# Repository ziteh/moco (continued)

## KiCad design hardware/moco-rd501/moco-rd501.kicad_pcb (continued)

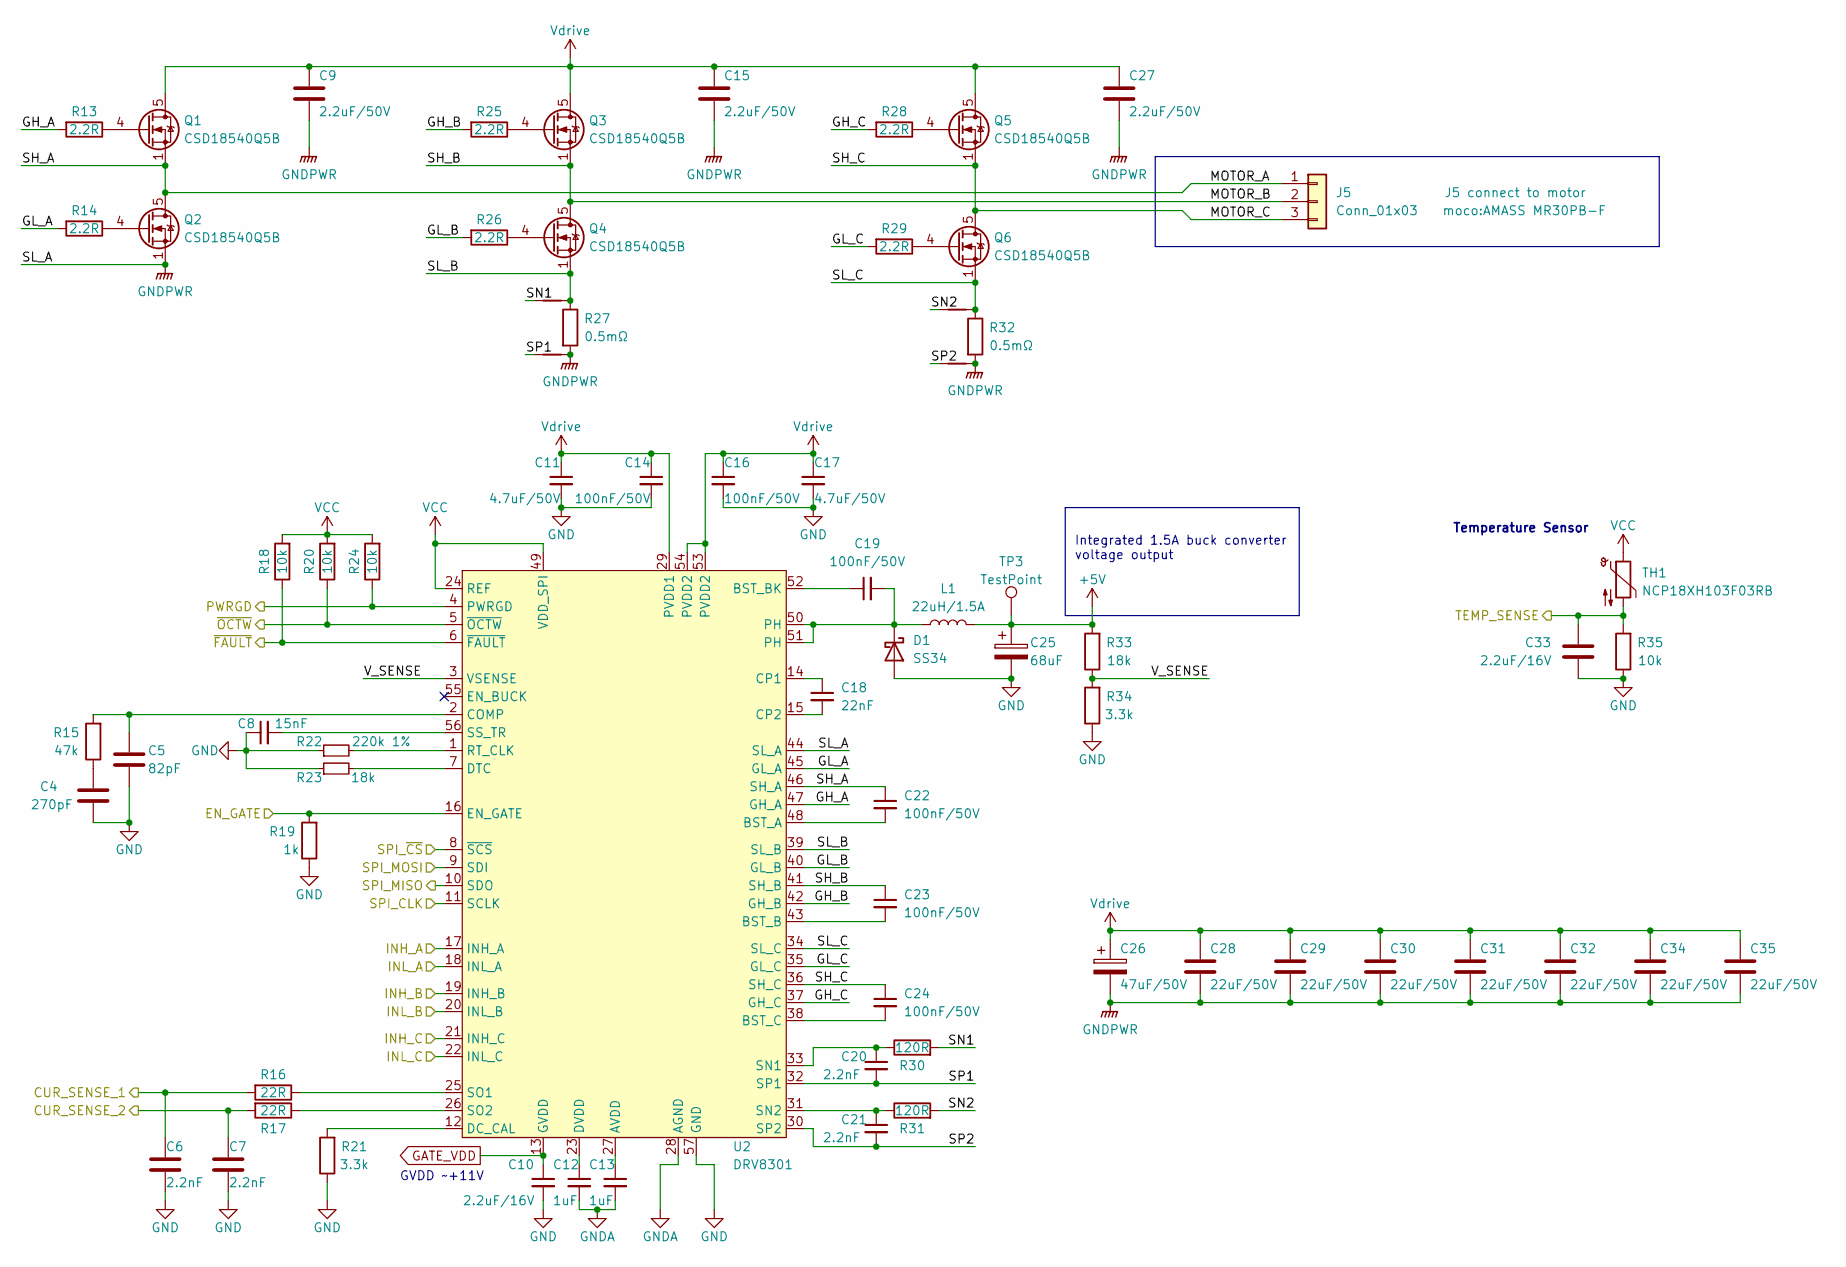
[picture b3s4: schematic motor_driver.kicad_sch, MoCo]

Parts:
C4: 270pF; C_0402_1005Metric; MFR.Part # GCM1555C1H271JA16D; JLCPCB Part # C524551
C5: 82pF; C_0402_1005Metric; MFR.Part # CC0402JRNPO9BN820; JLCPCB Part # C107011
C6, C7, C20, C21: 2.2nF; C_0603_1608Metric; MFR.Part # 0603B222K500NT; JLCPCB Part # C1604
C8: 15nF; C_0402_1005Metric; MFR.Part # CC0402KRX7R9BB153; JLCPCB Part # C114405
C9, C15, C27: 2.2uF/50V; C_1206_3216Metric; MFR.Part # CL31B225KBHNNNE; JLCPCB Part # C50254
C10, C33: 2.2uF/16V; C_0402_1005Metric; MFR.Part # 0402X225K160NT; JLCPCB Part # C501836
C11, C17: 4.7uF/50V; C_1206_3216Metric; MFR.Part # 1206B475K500NT; JLCPCB Part # C29823
C12, C13: 1uF; C_0402_1005Metric; MFR.Part # CL05A105KA5NQNC; JLCPCB Part # C52923
C14, C16, C19, C22, C23, C24: 100nF/50V; C_0603_1608Metric; MFR.Part # CC0603KRX7R9BB104; JLCPCB Part # C14663
C18: 22nF; C_0402_1005Metric; MFR.Part # 0402B223K500NT; JLCPCB Part # C1532
C25: 68uF; CP_EIA-6032-28_Kemet-C; MFR.Part # TAJC686K016RNJ; JLCPCB Part # C7220
C26: 47uF/50V; CP_Elec_6.3x7.7; MFR.Part # VES470M1HTR-0607; JLCPCB Part # C108053
C28, C29, C30, C31, C32, C34, C35: 22uF/50V; C_1210_3225Metric_Pad1.33x2.70mm_HandSolder
D1: SS34; D_SMA; MFR.Part # SS34; JLCPCB Part # C8678
J5: Conn_01x03; AMASS MR30PB-F; MFR.Part # MR30PB-F
L1: 22uH/1.5A; L_Bourns-SRN8040_8x8.15mm; MFR.Part # CKCS8040-22uH/M; JLCPCB Part # C354640
NT1, NT2, NT3, NT4: NetTie_2; NetTie-2_SMD_Pad0.5mm
Q1, Q2, Q3, Q4, Q5, Q6: CSD18540Q5B; TDSON-8-1; MFR.Part # CSD18540Q5B; JLCPCB Part # C86513
R13, R14, R25, R26, R28, R29: 2.2R; R_0603_1608Metric; MFR.Part # 0603WAF220KT5E; JLCPCB Part # C22939
R15: 47k; R_0402_1005Metric; MFR.Part # 0402WGF4702TCE; JLCPCB Part # C25792
R16, R17: 22R; R_0402_1005Metric; MFR.Part # 0402WGF220JTCE; JLCPCB Part # C25092
R18, R20, R24, R35: 10k; R_0402_1005Metric; MFR.Part # 0402WGF1002TCE; JLCPCB Part # C25744
R19: 1k; R_0402_1005Metric; MFR.Part # 0402WGF1001TCE; JLCPCB Part # C11702
R21, R34: 3.3k; R_0402_1005Metric; MFR.Part # 0402WGF3301TCE; JLCPCB Part # C25890
R22: 220k 1%; R_0402_1005Metric; MFR.Part # 0402WGF2203TCE; JLCPCB Part # C25767
R23, R33: 18k; R_0402_1005Metric; MFR.Part # 0402WGF1802TCE; JLCPCB Part # C25762
R27, R32: 0.5mΩ; R_2512_6332Metric; MFR.Part # ASR-M-3-0.5F; JLCPCB Part # C469426
R30, R31: 120R; R_0402_1005Metric; MFR.Part # 0402WGF1200TCE; JLCPCB Part # C25079
TH1: NCP18XH103F03RB; R_0603_1608Metric; MFR.Part # NCP18XH103F03RB; JLCPCB Part # C13564
TP3: TestPoint; TestPoint_Pad_D2.0mm
U2: DRV8301; HTSSOP-56-1EP_6.1x14mm_P0.5mm_EP3.61x6.35mm; MFR.Part # DRV8301DCAR; JLCPCB Part # C98969

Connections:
+5V: C25.1, L1.2, R33.2, TP3.1; also elsewhere on the board
/EN_GATE: R19.2, U2.16 (EN_GATE); also elsewhere on the board
/MCU/CURR_SENSE_1: C6.1, R16.2; also elsewhere on the board
/MCU/CURR_SENSE_2: C7.1, R17.2; also elsewhere on the board
/MCU/PWM_AH: U2.17 (INH_A); also elsewhere on the board
/MCU/PWM_AL: U2.18 (INL_A); also elsewhere on the board
/MCU/PWM_BH: U2.19 (INH_B); also elsewhere on the board
/MCU/PWM_BL: U2.20 (INL_B); also elsewhere on the board
/MCU/PWM_CH: U2.21 (INH_C); also elsewhere on the board
/MCU/PWM_CL: U2.22 (INL_C); also elsewhere on the board
/MCU/TEMP_SENSE: C33.1, R35.2, TH1.2; also elsewhere on the board
/Motor Driver/GH_A: R13.2, U2.47 (GH_A)
/Motor Driver/GH_B: R25.2, U2.42 (GH_B)
/Motor Driver/GH_C: R28.2, U2.37 (GH_C)
/Motor Driver/GL_A: R14.2, U2.45 (GL_A)
/Motor Driver/GL_B: R26.2, U2.40 (GL_B)
/Motor Driver/GL_C: R29.2, U2.35 (GL_C)
/Motor Driver/MOTOR_A: C22.1, J5.1, Q1.1 (S), Q1.2 (S), Q1.3 (S), Q2.5 (D), U2.46 (SH_A)
/Motor Driver/MOTOR_B: C23.1, J5.2, Q3.1 (S), Q3.2 (S), Q3.3 (S), Q4.5 (D), U2.41 (SH_B)
/Motor Driver/MOTOR_C: C24.1, J5.3, Q5.1 (S), Q5.2 (S), Q5.3 (S), Q6.5 (D), U2.36 (SH_C)
/Motor Driver/PWRGD: R24.1, U2.4 (PWRGD)
/Motor Driver/SL_B: NT1.2, Q4.1 (S), Q4.2 (S), Q4.3 (S), R27.1, U2.39 (SL_B)
/Motor Driver/SL_C: NT3.2, Q6.1 (S), Q6.2 (S), Q6.3 (S), R32.1, U2.34 (SL_C)
/Motor Driver/SN1: NT1.1, R30.2
/Motor Driver/SN2: NT3.1, R31.2
/Motor Driver/SP1: C20.2, NT2.1, U2.32 (SP1)
/Motor Driver/SP2: C21.2, NT4.1, U2.30 (SP2)
/Motor Driver/V_SENSE: R33.1, R34.2, U2.3 (VSENSE)
/Motor Driver/~OCTW: R20.1, U2.5 (~OCTW)
/SPI_CLK: U2.11 (SCLK); also elsewhere on the board
/SPI_DRIVER_~CS: U2.8 (~SCS); also elsewhere on the board
/SPI_MISO: U2.10 (SDO); also elsewhere on the board
/SPI_MOSI: U2.9 (SDI); also elsewhere on the board
/~FAULT: R18.1, U2.6 (~FAULT); also elsewhere on the board
GATE_VDD: C10.1, U2.13 (GVDD)
GND: C4.2, C5.2, C6.2, C7.2, C8.1, C9.2, C10.2, C11.2, C12.2, C13.2, C14.2, C15.2, C16.2, C17.2, C25.2, C26.2, C27.2, C28.2, C29.2, C30.2, C31.2, C32.2, C33.2, C34.2, C35.2, D1.2 (A), NT2.2, NT4.2, Q2.1 (S), Q2.2 (S), Q2.3 (S), R19.1, R21.1, R22.1, R23.1, R27.2, R32.2, R34.1, R35.1, U2.28 (AGND), U2.44 (SL_A), U2.57 (GND); also elsewhere on the board
unnamed: C4.1, R15.1
unnamed: C5.1, R15.2, U2.2 (COMP)
unnamed: C8.2, U2.56 (SS_TR)
unnamed: C12.1, U2.23 (DVDD)
unnamed: C13.1, U2.27 (AVDD)
unnamed: C18.1, U2.14 (CP1)
unnamed: C18.2, U2.15 (CP2)
unnamed: C19.1, U2.52 (BST_BK)
unnamed: C19.2, D1.1 (K), L1.1, U2.50 (PH), U2.51 (PH)
unnamed: C20.1, R30.1, U2.33 (SN1)
unnamed: C21.1, R31.1, U2.31 (SN2)
unnamed: C22.2, U2.48 (BST_A)
unnamed: C23.2, U2.43 (BST_B)
unnamed: C24.2, U2.38 (BST_C)
unnamed: Q1.4 (G), R13.1
unnamed: Q2.4 (G), R14.1
unnamed: Q3.4 (G), R25.1
unnamed: Q4.4 (G), R26.1
unnamed: Q5.4 (G), R28.1
unnamed: Q6.4 (G), R29.1
unnamed: R16.1, U2.25 (SO1)
unnamed: R17.1, U2.26 (SO2)
unnamed: R21.2, U2.12 (DC_CAL)
unnamed: R22.2, U2.1 (RT_CLK)
unnamed: R23.2, U2.7 (DTC)
VCC: R18.2, R20.2, R24.2, TH1.1, U2.24 (REF), U2.49 (VDD_SPI); also elsewhere on the board
Vdrive: C9.1, C11.1, C14.1, C15.1, C16.1, C17.1, C26.1, C27.1, C28.1, C29.1, C30.1, C31.1, C32.1, C34.1, C35.1, Q1.5 (D), Q3.5 (D), Q5.5 (D), U2.29 (PVDD1), U2.53 (PVDD2), U2.54 (PVDD2); also elsewhere on the board

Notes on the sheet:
Integrated 1.5A buck converter voltage output
Temperature Sensor
GVDD ~+11V

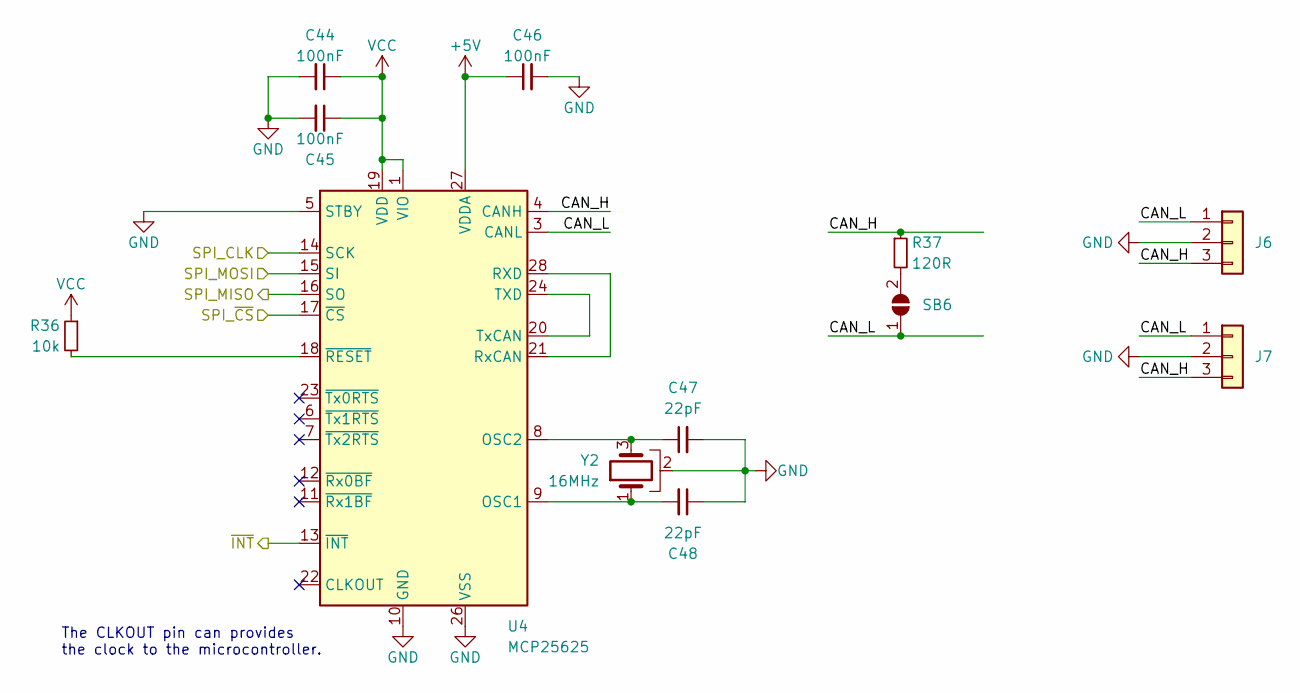
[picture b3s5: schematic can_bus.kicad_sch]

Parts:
C44, C45, C46: 100nF; C_0402_1005Metric; MFR.Part # CL05B104KO5NNNC; JLCPCB Part # C1525
C47, C48: 22pF; C_0402_1005Metric; MFR.Part # 0402CG220J500NT; JLCPCB Part # C1555
J6, J7: Conn_02x02_Top_Bottom; JST_GH_SM03B-GHS-TB_1x03-1MP_P1.25mm_Horizontal; MFR.Part # GH1.25-3PWBPZ; JLCPCB Part # C2829252
R36: 10k; R_0402_1005Metric; MFR.Part # 0402WGF1002TCE; JLCPCB Part # C25744
R37: 120R; R_0402_1005Metric; MFR.Part # 0402WGF1200TCE; JLCPCB Part # C25079
SB6: SolderJumper_2_Open; SolderJumper-2_P1.3mm_Open_TrianglePad1.0x1.5mm
U4: MCP25625; QFN-28-1EP_6x6mm_P0.65mm_EP4.25x4.25mm; MFR.Part # MCP25625T-E/ML; JLCPCB Part # C191253
Y2: 16MHz; Crystal_SMD_3225-4Pin_3.2x2.5mm; MFR.Part # X322516MLB4SI; JLCPCB Part # C13738

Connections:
+5V: C46.1, U4.27 (VDDA); also elsewhere on the board
/CAN BUS/CAN_H: J6.3, J7.3, R37.1, U4.4 (CANH)
/CAN BUS/CAN_L: J6.1, J7.1, SB6.1 (A), U4.3 (CANL)
/CAN BUS/~INT: U4.13 (~INT); also elsewhere on the board
/SPI_CAN_~CS: U4.17 (~CS); also elsewhere on the board
/SPI_CLK: U4.14 (SCK); also elsewhere on the board
/SPI_MISO: U4.16 (SO); also elsewhere on the board
/SPI_MOSI: U4.15 (SI); also elsewhere on the board
GND: C44.2, C45.2, C46.2, C47.2, C48.1, J6.2, J7.2, U4.5 (STBY), U4.10 (GND), U4.26 (VSS), Y2.2; also elsewhere on the board
unnamed: C47.1, U4.8 (OSC2), Y2.3
unnamed: C48.2, U4.9 (OSC1), Y2.1
unnamed: R36.2, U4.18 (~RESET)
unnamed: R37.2, SB6.2 (B)
unnamed: U4.20 (TxCAN), U4.24 (TXD)
unnamed: U4.21 (RxCAN), U4.28 (RXD)
VCC: C44.1, C45.1, R36.1, U4.1 (VIO), U4.19 (VDD); also elsewhere on the board

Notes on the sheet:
The CLKOUT pin can provides the clock to the microcontroller.

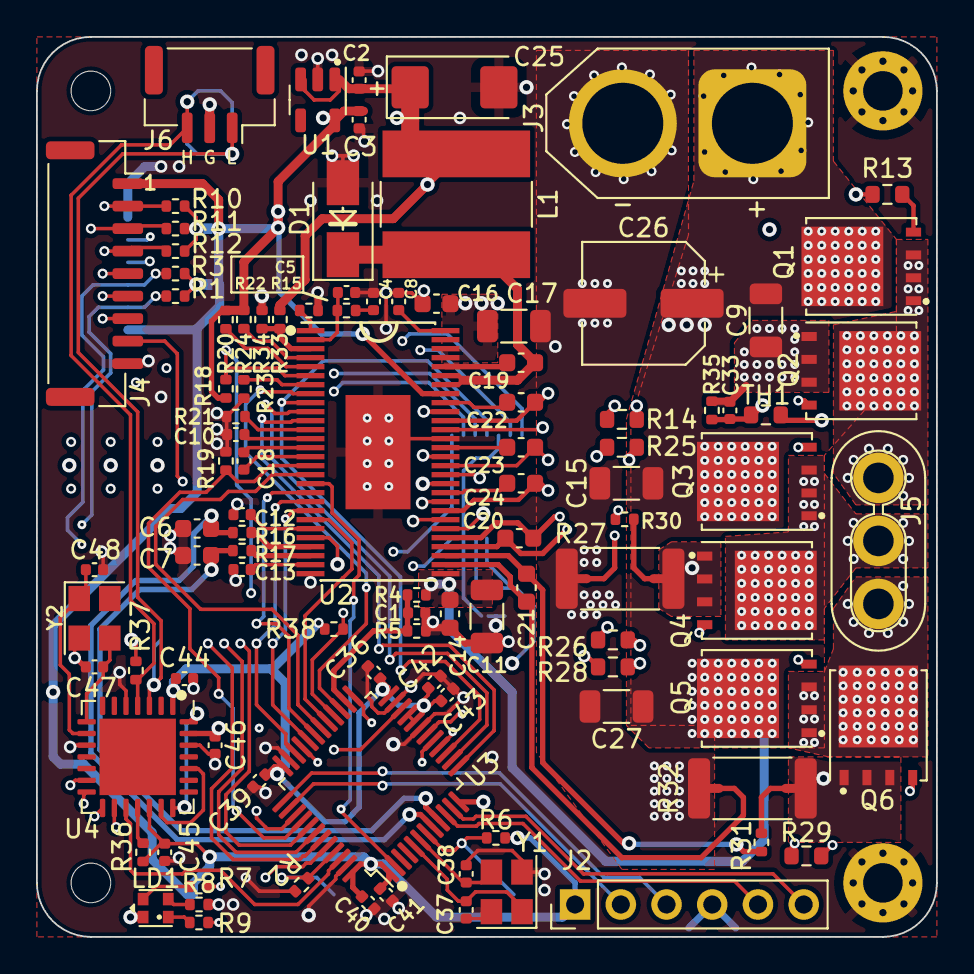
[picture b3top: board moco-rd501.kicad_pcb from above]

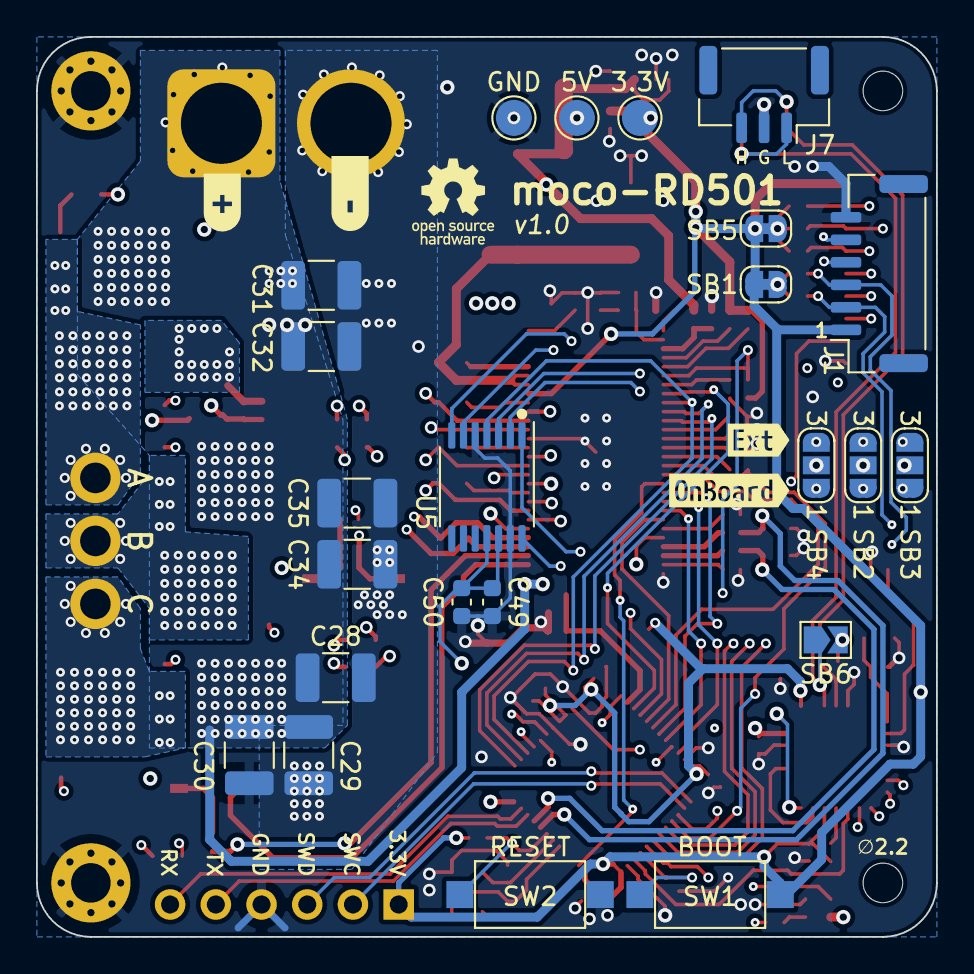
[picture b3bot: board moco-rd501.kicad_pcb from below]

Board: 4 copper layers, 50.0 x 50.0 mm, 135 parts (27 on the bottom side), 103 nets.

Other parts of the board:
kibuzzard-638C8B7C: G***; kibuzzard-638C8B7C
kibuzzard-638C8BCF: G***; kibuzzard-638C8BCF
kibuzzard-638C8E4D: G***; kibuzzard-638C8E4D
kibuzzard-638C8E29: G***; kibuzzard-638C8E29

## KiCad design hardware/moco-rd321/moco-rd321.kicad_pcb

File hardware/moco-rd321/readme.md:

# moco-RD321

- 6.7V~35V, 12A
- 3-Phase low-side current sensing. OP-Amp Gain=6.74, Shunt resistor=20mΩ
- Overcurrent detection. Ith=30A @ OC_COMPth=500mV
- Input voltage sensing
- 32x32mm square PCB, 4xM2 mounting holes
- [STSPIN32F0A](https://www.st.com/en/motor-drivers/stspin32f0a.html) 3-phase gate driver with embdded MCU SiP
  - STM32F031C6 48MHz, 4KB SRAM, 32KB Flash
  - 600mA sink/source gate drivers, integrated bootstrap diodes
  - 12V LDO and 3.3V buck
- [SiZ250DT](https://www.vishay.com/en/product/77227/) Dual N-MOSFET, 60V, 38A, 3.3x3.3mm
- MA702 magnetic encoder, SPI
- 2x04 2.54mm Pin header for debug, JST SM03B-SRSS-TB 1x03 for Serial and I2C

## Pinmap

| Description              | Analog IC    | STM32 | STM32 Func       |
| ------------------------ | ------------ | ----- | ---------------- |
| High-side U              | HS1          | PA8   | TIM1_CH1         |
| High-side V              | HS2          | PA9   | TIM1_CH2         |
| High-side W              | HS3          | PA10  | TIM1_CH3         |
| Low-side U               | LS1          | PB13  | TIM1_CH1N        |
| Low-side V               | LS2          | PB14  | TIM1_CH2N        |
| Low-side W               | LS3          | PB15  | TIM1_CH3N        |
| OC threshold select 1    | OC_TH_STBY1  | PF7   | Push-pull output |
| OC threshold select 2    | OC_TH_STBY2  | PF6   | Push-pull output |
| OC protection selection  | OC_SEL       | PA11  | Push-pull output |
| OC comparator output     | OC_COMP_INT  | PB12  | TIM1_BKIN        |
| OC comparator output     | OC_COMP_INT2 | PA12  | TIM1_ETR         |
| Current sense U          | OP3O         | PA0   | ADC_IN0          |
| Current sense V          | OP2O         | PA1   | ADC_IN1          |
| Current sense W          | OP1O         | PB1   | ADC_IN9          |
| VM sense                 | --           | PA4   | ADC_IN4          |
| SPI SCLK                 | --           | PA5   | SPI1             |
| SPI MISO                 | --           | PA6   | SPI1             |
| SPI MOSI                 | --           | PA7   | SPI1             |
| SPI nCS MA702            | --           | PA15  |                  |
| USART Tx                 | --           | PA2   | USART1           |
| USART Rx                 | --           | PA3   | USART1           |
| I2C SCL                  | --           | PB6   | I2C1             |
| I2C SDA                  | --           | PB7   | I2C1             |
| SWDIO                    | --           | PA13  |                  |
| SWCLK                    | --           | PA14  |                  |
| Connected to GND         | --           | BOOT0 |                  |
| User LED (Red)           | --           | PF0   | Active HIGH      |
| 12V indicator LED (Blue) | --           | --    |                  |

> - Unused GPIOs inside the package should be config to output low: PB0, PB2, PB3, PB4, PB5, PB8, PB9, PB10, PB11, PC13, PC14, PC15.
> - OC_TH_STBY1 and OC_TH_STBY2 should be HIGH for 500mV OC threshold.
> - For analog IC, the GPIO input config without pull-up or -down is always allowed.

## PCB

### Jumper

If input voltage (i.e. VM)<15V then close `SB1` to connect VM pin and VREG12 pin.

### Board Characteristics

- Copper layer count: 4
- Board overall dimensions: 32 x 32 mm
- Min track/spacing: 0.13 mm / 0.13 mm
- Min hole diameter: 0.3 mm
- Castellated pads: No
- Edge card connectors: No
- Plated board edge: No
- 1oz copper

## SPI

MA702 encoder SPI:
- Mode:
  - 0 (CPOL=0, CPHA=0) or 1 (CPOL=1, CPHA=1)
  - Data sampled on first edge
- 16-bit data frame
- MSB first
- nCS pin active low
- 25MHz clock

## MCU

| STSPIN32*x*                         | [F0](https://www.st.com/en/motor-drivers/stspin32f0.html) | [F0***A***](https://www.st.com/en/motor-drivers/stspin32f0a.html) | [F0***B***](https://www.st.com/en/motor-drivers/stspin32f0b.html) |
| ----------------------------------- | --------------------------------------------------------- | ----------------------------------------------------------------- | ----------------------------------------------------------------- |
| Operating voltage                   | 8~45V                                                     | 6.7~45V                                                           | 6.7~45V                                                           |
| OP-Amps                             | 4                                                         | 3                                                                 | 1                                                                 |
| GPIOs                               | 15                                                        | 16                                                                | 20                                                                |
| BOOT0 pin                           | --                                                        | Yes                                                               | Yes                                                               |
| 3FG decoding logic for Hall sensors | Yes                                                       | --                                                                | --                                                                |
| Comparator                          | OCP                                                       | OCP and current control                                           | OCP and current control                                           |
| Package                             | QFN 7x7mm 1EP                                             | QFN 7x7mm 1EP                                                     | QFN 7x7mm 1EP                                                     |

> [Solved: STSPIN32F0 vs STSPIN32F0A vs STSPIN32F0B - STMicroelectronics Community](https://community.st.com/t5/power-management/stspin32f0-vs-stspin32f0a-vs-stspin32f0b/td-p/273388)

## Reference

- [qwertpas/O32controller: Miniature closed-loop controller for brushless DC motors](https://github.com/qwertpas/O32controller)
- [STspin32G4 support - hardware support - SimpleFOC Community](https://community.simplefoc.com/t/stspin32g4-support/2027/6?page=3)
- ST AN5397 *"Current Sensing in motion control applications"*
- ST AN4999 *"STSPIN32F0/F0A/F0B overcurrent protection"*
- ST DB3364 *"STEVAL-SPIN3202: STSPIN32F0A advanced 3-phase BLDC driver with embedded STM32 MCU single shunt evaluation board"*
- ST DB4049 *"EVALKIT-ROBOT-1: Compact reference design kit for robotics and automation based on STSPIN32F0A"*
- ST DB3798 *"STEVAL-ESC002V1: Electronic Speed Controller reference design based on STSPIN32F0A"*
- TI SLUA887 *"Bootstrap Circuitry Selection for Half-Bridge Configurations"*
- Diodes DN1156 *"Gate Drivers in BLDC Motors"*

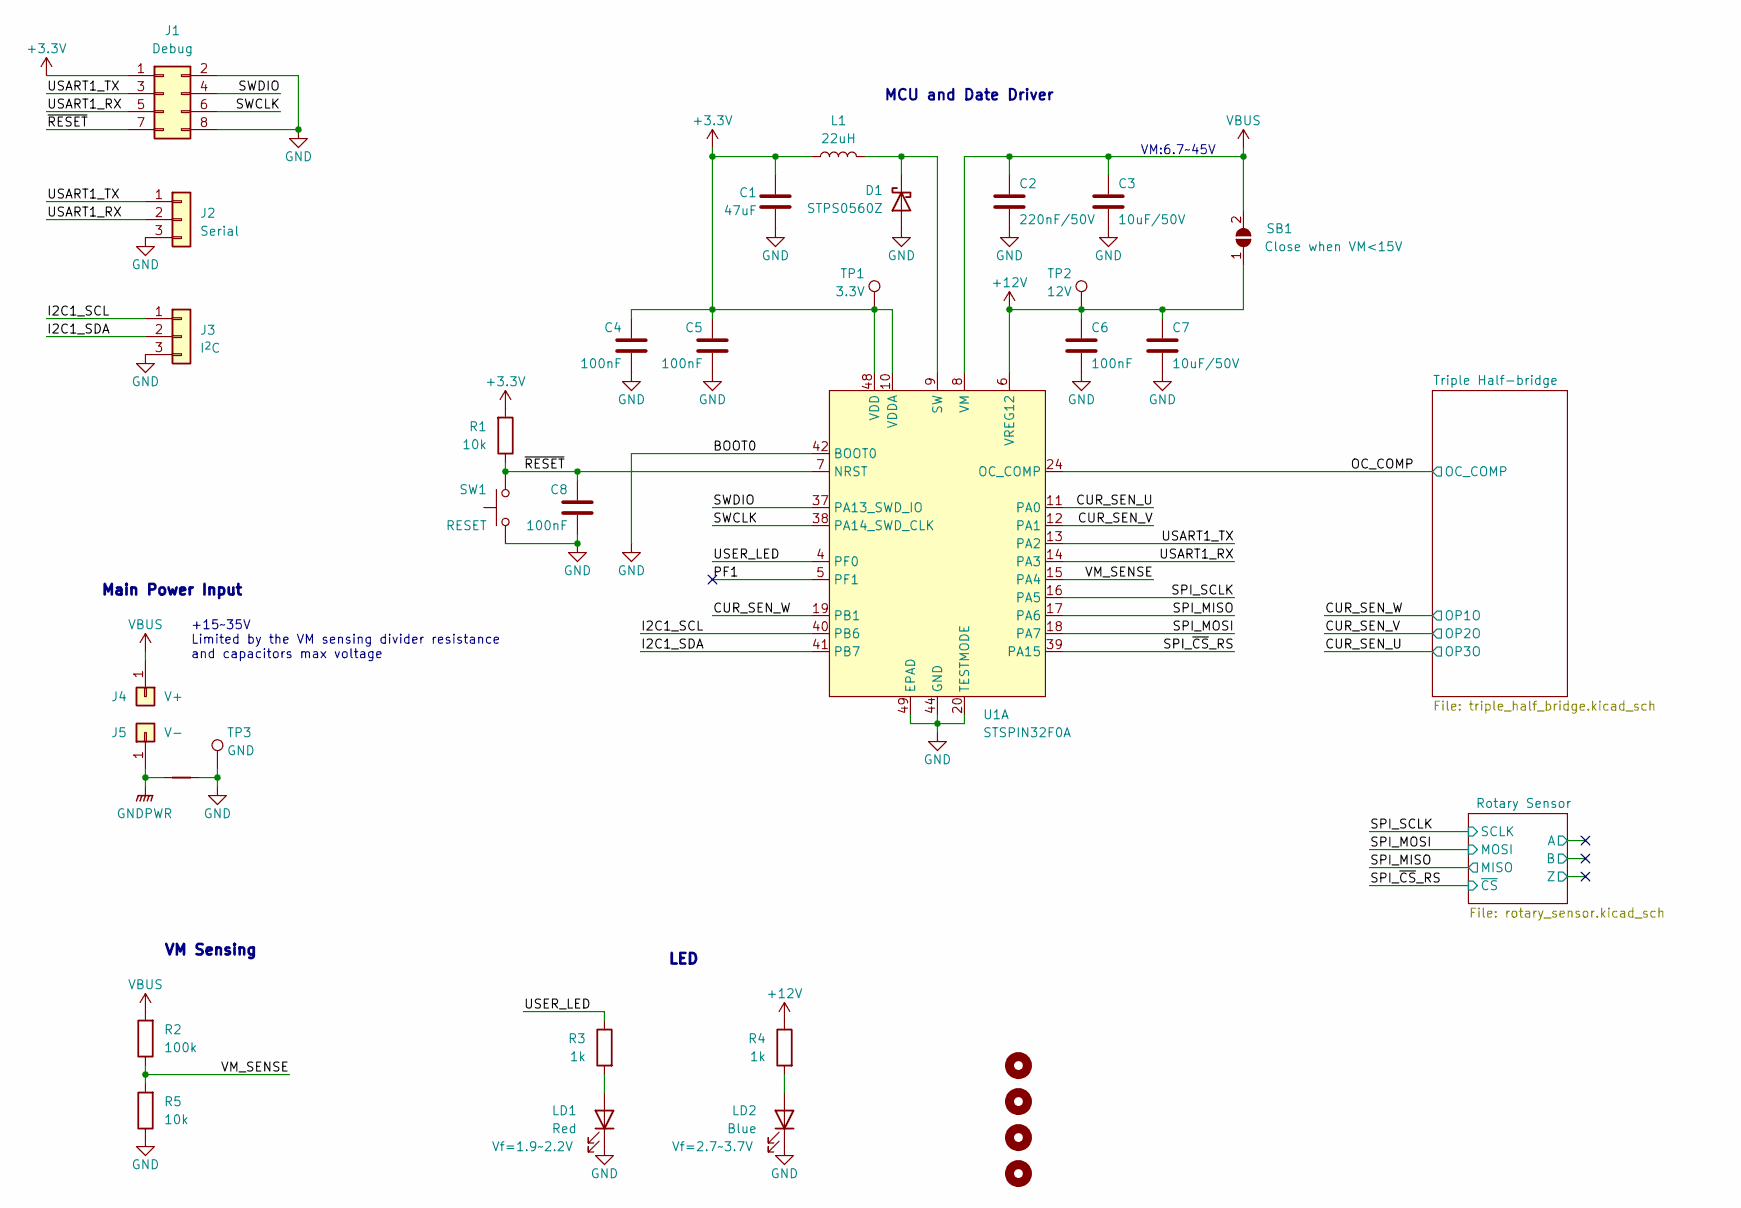
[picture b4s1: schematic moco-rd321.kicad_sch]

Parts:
C1: 47uF; C_0805_2012Metric; MFR. Part# CL21A476MQYNNNE; LCSC C16780
C2: 220nF/50V; C_0805_2012Metric; MFR. Part# CL21B224KBFNNNE; LCSC C5378
C3, C7: 10uF/50V; C_0805_2012Metric; MFR. Part# GRM21BR61H106KE43L; LCSC C440198
C4, C5, C6, C8: 100nF; C_0402_1005Metric; MFR. Part# CL05B104KB54PNC; LCSC C307331
D1: STPS0560Z; D_SOD-123F; MFR. Part# STPS0560Z; LCSC C99285
H1, H2, H3, H4: MountingHole; MountingHole_2.2mm_M2_ISO14580
J1: Debug; PinHeader_2x04_P2.54mm_Vertical
J2: Serial; JST_SH_SM03B-SRSS-TB_1x03-1MP_P1.00mm_Horizontal; MFR. Part# SM03B-SRSS-TB(LF)(SN); LCSC C160403
J3: I^{2}C; JST_SH_SM03B-SRSS-TB_1x03-1MP_P1.00mm_Horizontal; MFR. Part# SM03B-SRSS-TB(LF)(SN); LCSC C160403
J4: V+; wire_2.2mm_rectagnel
J5: V-; wire_2.2mm
L1: 22uH; L_Taiyo-Yuden_MD-3030; MFR. Part# YNR3015-220M; LCSC C497564
LD1: Red; LED_0603_1608Metric; MFR. Part# KT-0603R; LCSC C2286
LD2: Blue; LED_0603_1608Metric; MFR. Part# 19-217/GHC-YR1S2/3T; LCSC C72043
NT1: NetTie_2; NetTie-2_SMD_Pad0.5mm
R1, R5: 10k; R_0402_1005Metric; MFR. Part# 0402WGF1002TCE; LCSC C25744
R2: 100k; R_0402_1005Metric; MFR. Part# 0402WGF1003TCE; LCSC C25741
R3, R4: 1k; R_0402_1005Metric; MFR. Part# 0402WGF1001TCE; LCSC C11702
SB1: SolderJumper_2_Open; SolderJumper-2_P1.3mm_Open_RoundedPad1.0x1.5mm
SW1: RESET; SW_SPST_EVQP7C; MFR. Part# 3*4mm
TP1: 3.3V; TestPoint_Pad_D1.0mm
TP2: 12V; TestPoint_Pad_D1.0mm
TP3: GND; TestPoint_Pad_D1.0mm
U1: STSPIN32F0A; VFQFN-48_7x7_EP2.8mm_Pitch0.5mm; MFR. Part# STSPIN32F0A; LCSC C1520987

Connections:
+3.3V: C1.1, C4.1, C5.1, J1.1, L1.1, R1.2, TP1.1, U1.10 (VDDA), U1.48 (VDD); also elsewhere on the board
+12V: C6.1, C7.1, R4.1, SB1.1 (A), TP2.1, U1.6 (VREG12)
/CUR_SEN_U: U1.11 (PA0); also elsewhere on the board
/CUR_SEN_V: U1.12 (PA1); also elsewhere on the board
/CUR_SEN_W: U1.19 (PB1); also elsewhere on the board
/I2C1_SCL: J3.1, U1.40 (PB6)
/I2C1_SDA: J3.2, U1.41 (PB7)
/OC_COMP: U1.24 (OC_COMP); also elsewhere on the board
/PF1: U1.5 (PF1)
/SPI_MISO: U1.17 (PA6); also elsewhere on the board
/SPI_MOSI: U1.18 (PA7); also elsewhere on the board
/SPI_SCLK: U1.16 (PA5); also elsewhere on the board
/SPI_~CS_RS: U1.39 (PA15); also elsewhere on the board
/SWCLK: J1.6, U1.38 (PA14_SWD_CLK)
/SWDIO: J1.4, U1.37 (PA13_SWD_IO)
/USART1_RX: J1.5, J2.2, U1.14 (PA3)
/USART1_TX: J1.3, J2.1, U1.13 (PA2)
/USER_LED: R3.1, U1.4 (PF0)
/VM_SENSE: R2.1, R5.2, U1.15 (PA4)
/~RESET: C8.1, J1.7, R1.1, SW1.1, U1.7 (NRST)
GND: C1.2, C2.2, C3.2, C4.2, C5.2, C6.2, C7.2, C8.2, D1.2 (A), J1.2, J1.8, J2.3, J3.3, LD1.1 (K), LD2.1 (K), NT1.2, R5.1, SW1.2, TP3.1, U1.20 (TESTMODE), U1.42 (BOOT0), U1.44 (GND), U1.49 (EPAD); also elsewhere on the board
GNDPWR: J5.1, NT1.1; also elsewhere on the board
unnamed: D1.1 (K), L1.2, U1.9 (SW)
unnamed: LD1.2 (A), R3.2
unnamed: LD2.2 (A), R4.2
VBUS: C2.1, C3.1, J4.1, R2.2, SB1.2 (B), U1.8 (VM); also elsewhere on the board

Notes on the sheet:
+15~35V Limited by the VM sensing divider resistance and capacitors max voltage
VM Sensing
VM:6.7~45V
LED
Main Power Input
MCU and Date Driver

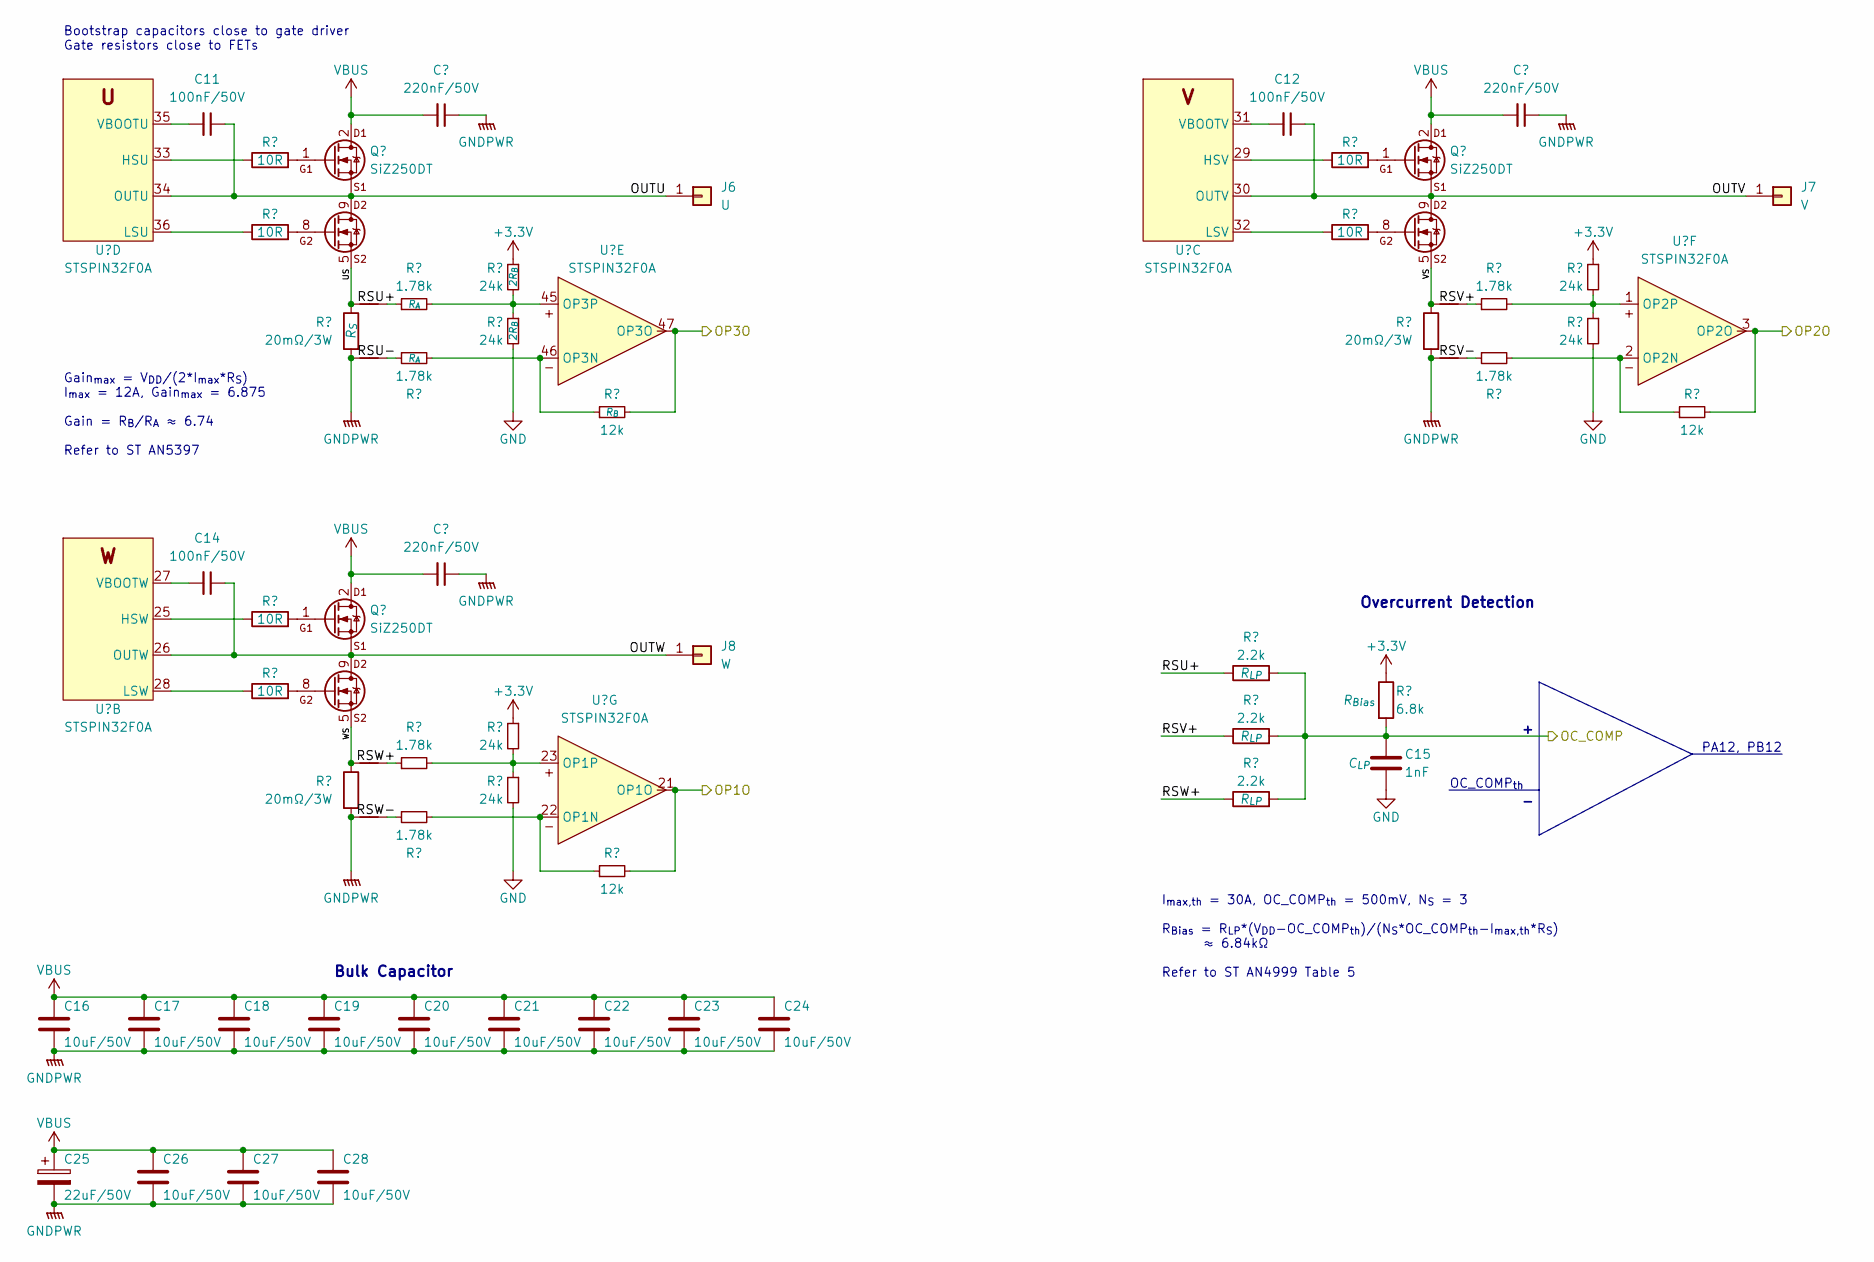
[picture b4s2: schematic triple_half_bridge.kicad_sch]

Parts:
C9, C10, C13: 220nF/50V; C_0805_2012Metric; MFR. Part# CL21B224KBFNNNE; LCSC C5378
C11, C12, C14: 100nF/50V; C_0402_1005Metric; MFR. Part# CL05B104KB54PNC; LCSC C307331
C15: 1nF; C_0402_1005Metric; MFR. Part# 0402B102K500NT; LCSC C1523
C16, C17, C18, C19, C20, C21, C22, C23, C24, C26, C27, C28: 10uF/50V; C_0805_2012Metric; MFR. Part# GRM21BR61H106KE43L; LCSC C440198
C25: 22uF/50V; CP_Elec_5x5.8; MFR. Part# EEEFT1H220AR; LCSC C336246
J6: U; wire_2.2mm
J7: V; wire_2.2mm
J8: W; wire_2.2mm
NT2, NT3, NT4, NT5, NT6, NT7: NetTie_2; NetTie-2_SMD_Pad0.5mm
Q1, Q2, Q3: SiZ250DT; PowerPAIR_3x3S_TP; MFR. Part# SIZ250DT-T1-GE3; LCSC C3279427
R6, R7, R8, R9, R22, R25: 10R; R_0402_1005Metric; MFR. Part# 0402WGF100JTCE; LCSC C25077
R10, R11, R15, R17, R27, R31: 24k; R_0402_1005Metric; MFR. Part# 0402WGF2402TCE; LCSC C25769
R12, R13, R18, R19, R28, R32: 1.78k; R_0402_1005Metric; MFR. Part# ARG02FTC1781; LCSC C284379
R14, R16, R30: 20mΩ/3W; R_2512_6332Metric; MFR. Part# CRA2512-FZ-R020ELF; LCSC C840620
R20, R21, R33: 12k; R_0402_1005Metric; MFR. Part# 0402WGF1202TCE; LCSC C25752
R23, R26, R29: 2.2k; R_0402_1005Metric; MFR. Part# 0402WGF2201TCE; LCSC C25879
R24: 6.8k; R_0402_1005Metric; MFR. Part# 0402WGF6801TCE; LCSC C25917
U1: STSPIN32F0A; VFQFN-48_7x7_EP2.8mm_Pitch0.5mm; MFR. Part# STSPIN32F0A; LCSC C1520987

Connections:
+3.3V: R10.1, R11.1, R24.1, R27.1; also elsewhere on the board
/CUR_SEN_U: R20.2, U1.47 (OP3O); also elsewhere on the board
/CUR_SEN_V: R21.2, U1.3 (OP2O); also elsewhere on the board
/CUR_SEN_W: R33.2, U1.21 (OP1O); also elsewhere on the board
/OC_COMP: C15.1, R23.2, R24.2, R26.2, R29.2; also elsewhere on the board
/Triple Half-bridge/OUTU: C11.1, J6.1, Q1.9 (S1D2), U1.34 (OUTU)
/Triple Half-bridge/OUTV: C12.1, J7.1, Q2.9 (S1D2), U1.30 (OUTV)
/Triple Half-bridge/OUTW: C14.1, J8.1, Q3.9 (S1D2), U1.26 (OUTW)
/Triple Half-bridge/RSU+: NT2.1, R12.1, R23.1
/Triple Half-bridge/RSU-: NT4.1, R18.1
/Triple Half-bridge/RSV+: NT3.1, R13.1, R26.1
/Triple Half-bridge/RSV-: NT5.1, R19.1
/Triple Half-bridge/RSW+: NT6.1, R28.1, R29.1
/Triple Half-bridge/RSW-: NT7.1, R32.1
/Triple Half-bridge/US: NT2.2, Q1.5 (S2), Q1.6 (S2), Q1.7 (S2), R14.1
/Triple Half-bridge/VS: NT3.2, Q2.5 (S2), Q2.6 (S2), Q2.7 (S2), R16.1
/Triple Half-bridge/WS: NT6.2, Q3.5 (S2), Q3.6 (S2), Q3.7 (S2), R30.1
GND: C15.2, R15.2, R17.2, R31.2; also elsewhere on the board
GNDPWR: C9.1, C10.1, C13.1, C16.2, C17.2, C18.2, C19.2, C20.2, C21.2, C22.2, C23.2, C24.2, C25.2, C26.2, C27.2, C28.2, NT4.2, NT5.2, NT7.2, R14.2, R16.2, R30.2; also elsewhere on the board
unnamed: Q1.1 (G1), R6.2
unnamed: Q1.8 (G2), R8.2
unnamed: Q2.1 (G1), R7.2
unnamed: Q2.8 (G2), R9.2
unnamed: Q3.1 (G1), R22.2
unnamed: Q3.8 (G2), R25.2
unnamed: R22.1, U1.25 (HSW)
unnamed: R25.1, U1.28 (LSW)
unnamed: C14.2, U1.27 (VBOOTW)
unnamed: R7.1, U1.29 (HSV)
unnamed: R9.1, U1.32 (LSV)
unnamed: C12.2, U1.31 (VBOOTV)
unnamed: R6.1, U1.33 (HSU)
unnamed: R8.1, U1.36 (LSU)
unnamed: C11.2, U1.35 (VBOOTU)
unnamed: R18.2, R20.1, U1.46 (OP3N)
unnamed: R10.2, R12.2, R15.1, U1.45 (OP3P)
unnamed: R19.2, R21.1, U1.2 (OP2N)
unnamed: R11.2, R13.2, R17.1, U1.1 (OP2P)
unnamed: R32.2, R33.1, U1.22 (OP1N)
unnamed: R27.2, R28.2, R31.1, U1.23 (OP1P)
VBUS: C9.2, C10.2, C13.2, C16.1, C17.1, C18.1, C19.1, C20.1, C21.1, C22.1, C23.1, C24.1, C25.1, C26.1, C27.1, C28.1, Q1.2 (D1), Q1.3 (D1), Q1.4 (D1), Q1.10 (D1), Q2.2 (D1), Q2.3 (D1), Q2.4 (D1), Q2.10 (D1), Q3.2 (D1), Q3.3 (D1), Q3.4 (D1), Q3.10 (D1); also elsewhere on the board

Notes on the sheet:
OC_COMP_{th}
Bootstrap capacitors close to gate driver Gate resistors close to FETs
Bulk Capacitor
PA12, PB12
Gain_{max} = V_{DD}/(2*I_{max}*R_{S}) I_{max} = 12A, Gain_{max} = 6.875 Gain = R_{B}/R_{A} ≈ 6.74 Refer to ST AN5397
Overcurrent Detection
I_{max,th} = 30A, OC_COMP_{th} = 500mV, N_{S} = 3 R_{Bias} = R_{LP}*(V_{DD}-OC_COMP_{th})/(N_{S}*OC_COMP_{th}-I_{max,th}*R_{S}) ≈ 6.84kΩ Refer to ST AN4999 Table 5

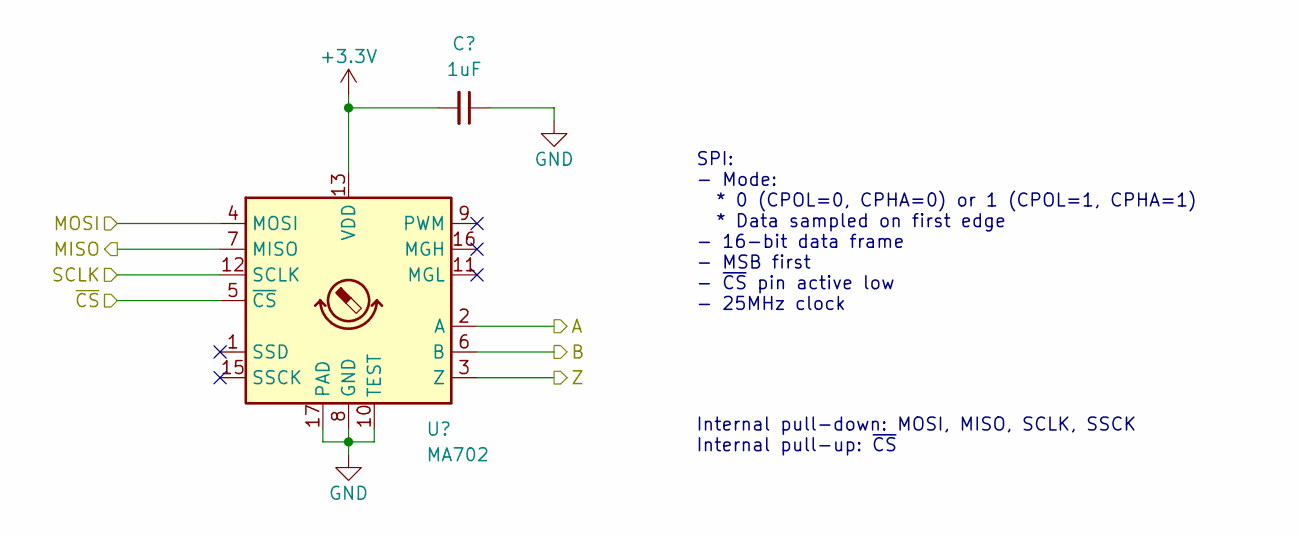
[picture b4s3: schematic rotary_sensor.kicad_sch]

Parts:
C29: 1uF; C_0402_1005Metric; MFR. Part# CL05A105KA5NQNC; LCSC C52923
U2: MA702; QFN-16-1EP_3x3mm_P0.5mm_EP1.75x1.75mm; MFR. Part# MA702GQ-Z

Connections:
+3.3V: C29.2, U2.13 (VDD); also elsewhere on the board
/ Rotary Sensor/A: U2.2 (A)
/ Rotary Sensor/B: U2.6 (B)
/ Rotary Sensor/Z: U2.3 (Z)
/SPI_MISO: U2.7 (MISO); also elsewhere on the board
/SPI_MOSI: U2.4 (MOSI); also elsewhere on the board
/SPI_SCLK: U2.12 (SCLK); also elsewhere on the board
/SPI_~CS_RS: U2.5 (~CS); also elsewhere on the board
GND: C29.1, U2.8 (GND), U2.10 (TEST), U2.17 (PAD); also elsewhere on the board

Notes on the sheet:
Internal pull-down: MOSI, MISO, SCLK, SSCK Internal pull-up: ~{CS}
SPI: - Mode: * 0 (CPOL=0, CPHA=0) or 1 (CPOL=1, CPHA=1) * Data sampled on first edge - 16-bit data frame - MSB first - ~{CS} pin active low - 25MHz clock

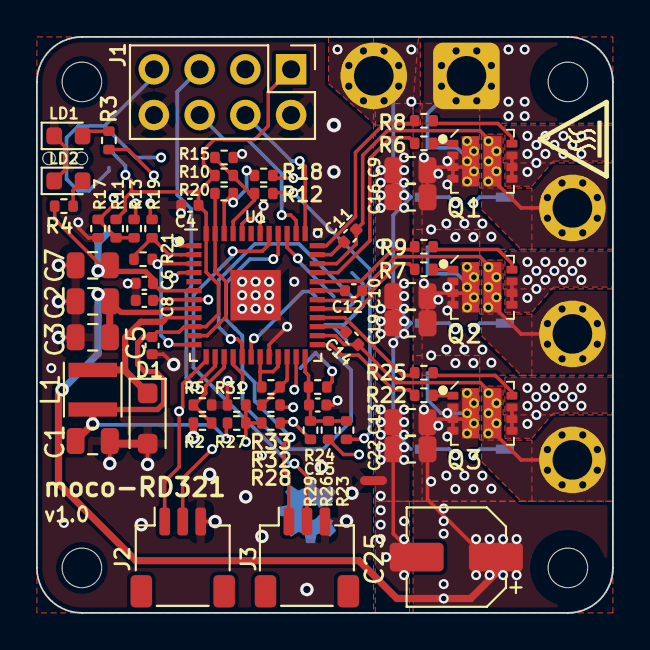
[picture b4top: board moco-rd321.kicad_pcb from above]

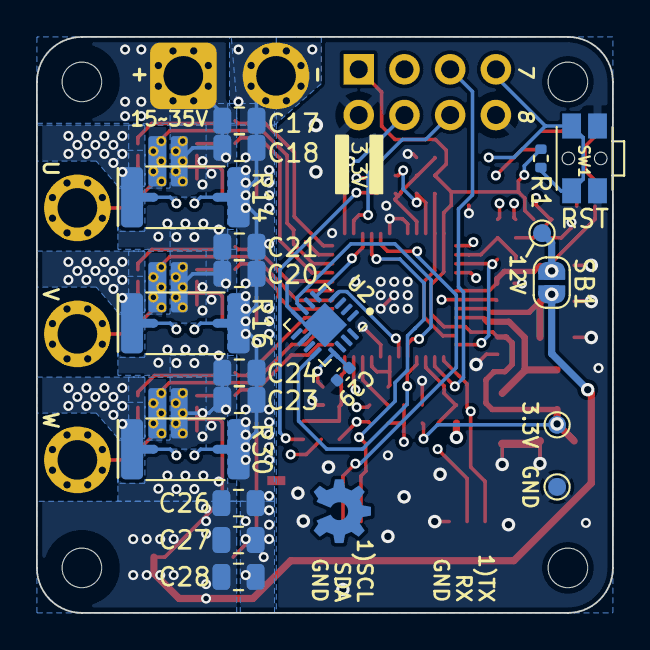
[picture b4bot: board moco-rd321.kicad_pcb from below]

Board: 4 copper layers, 32.0 x 32.0 mm, 95 parts (26 on the bottom side), 58 nets.
